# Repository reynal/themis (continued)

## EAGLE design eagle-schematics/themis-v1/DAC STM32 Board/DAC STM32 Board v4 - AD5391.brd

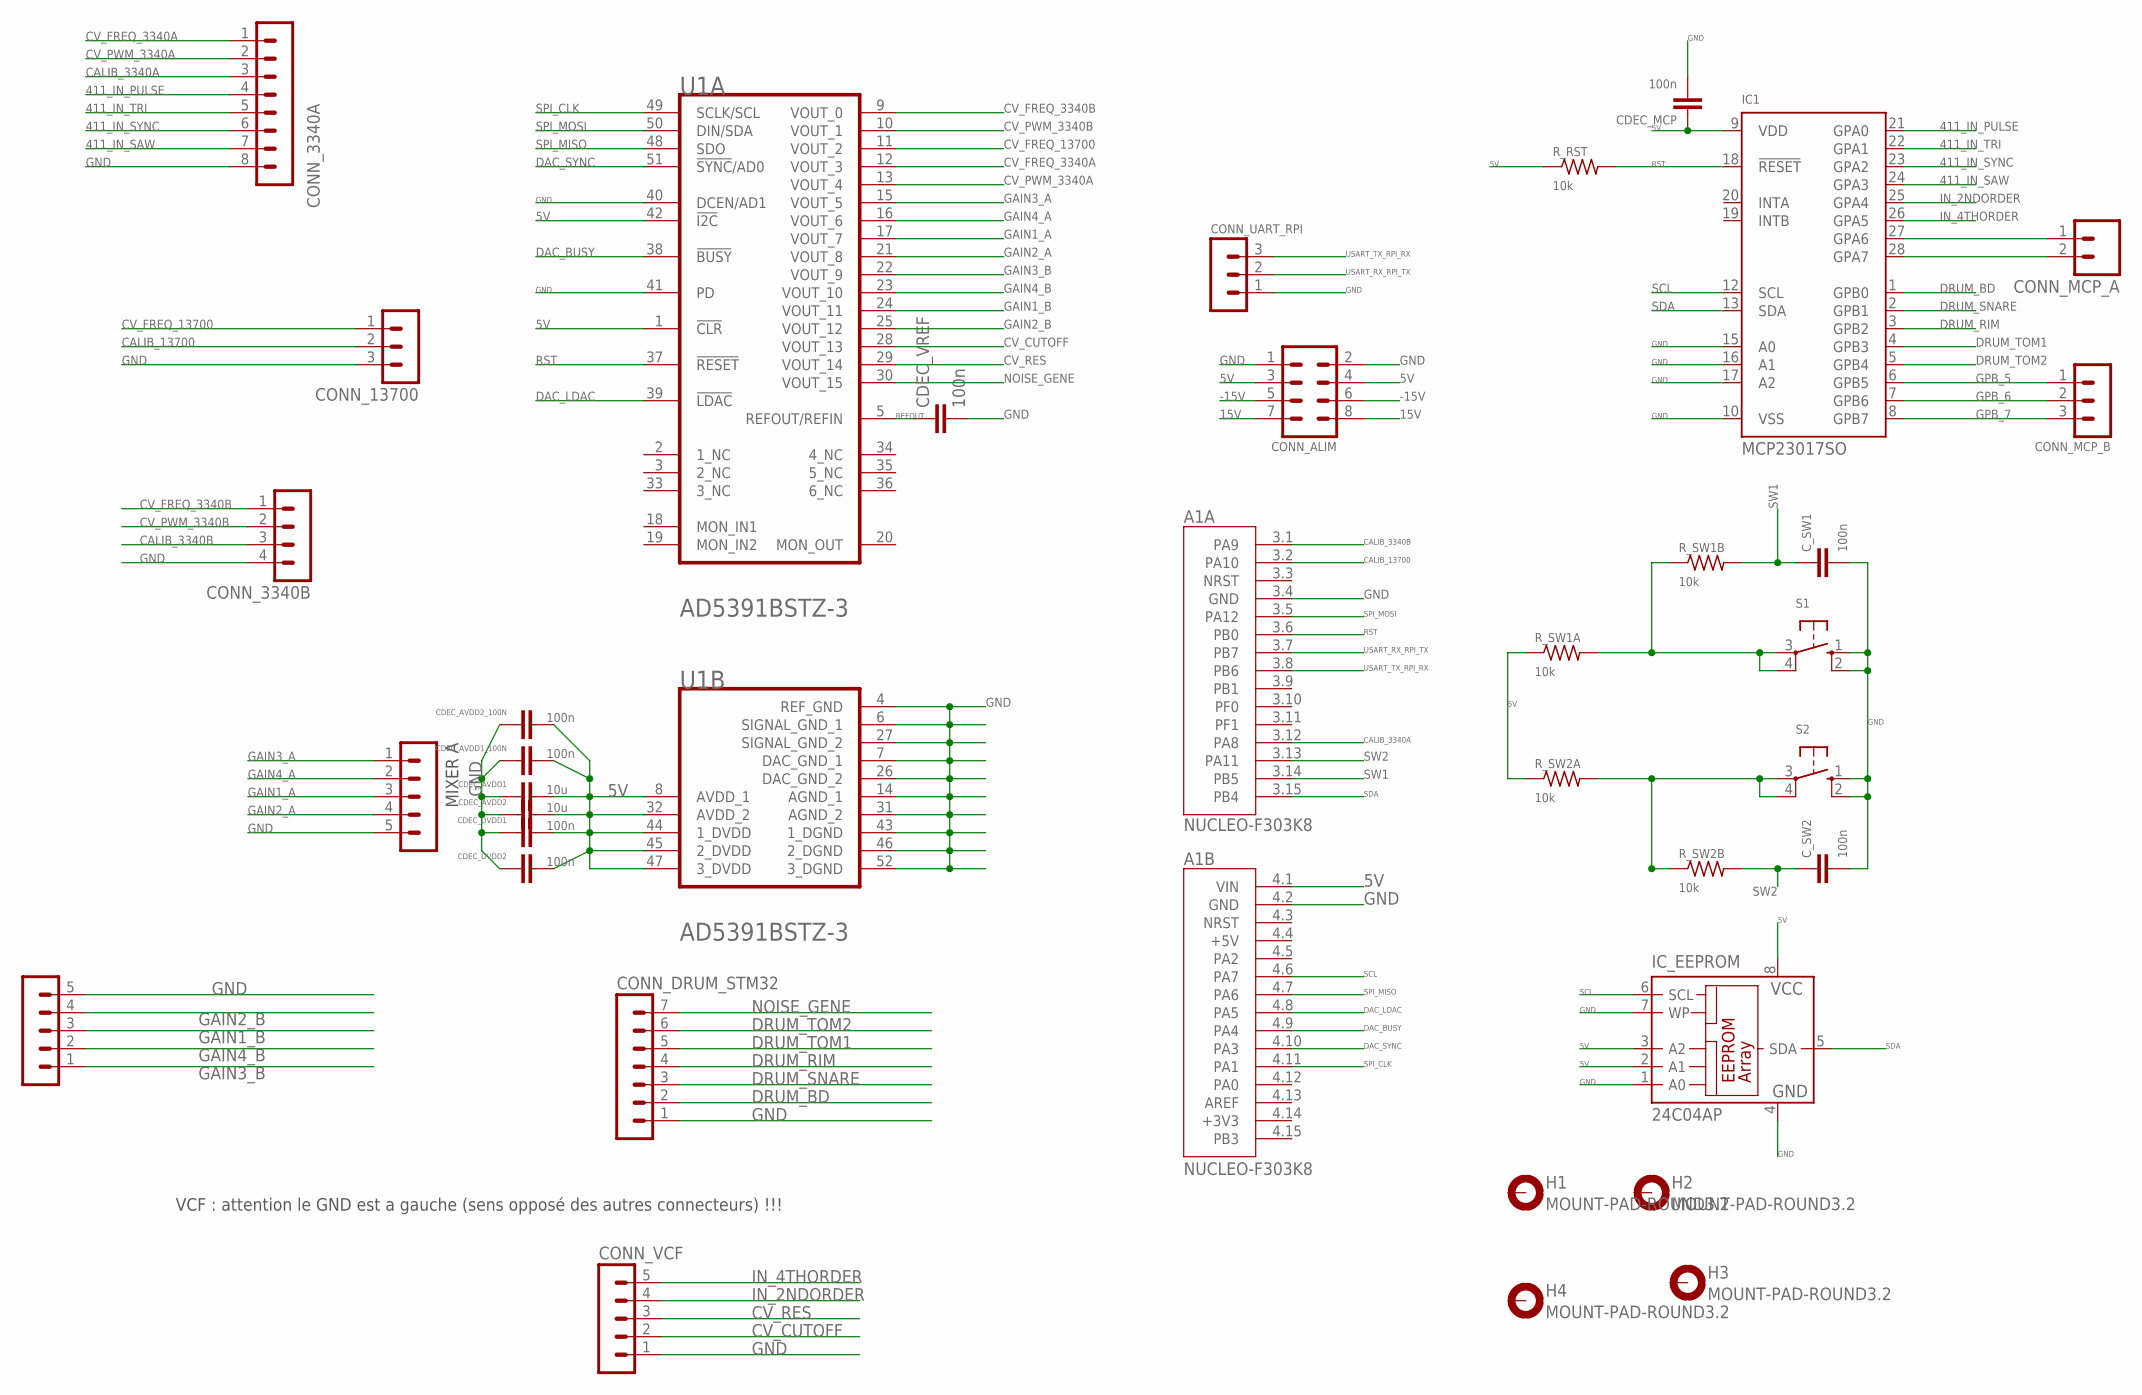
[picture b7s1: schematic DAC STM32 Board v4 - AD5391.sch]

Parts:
A1: NUCLEO-F303K8; MODULE_NUCLEO-F303K8
CDEC_AVDD1, CDEC_AVDD2: 10u; C050-030X075
CDEC_AVDD1_100N, CDEC_AVDD2_100N: 100n; C050-030X075
CDEC_DVDD1: 100n; C075-032X103
CDEC_DVDD2: 100n; C050-030X075
CDEC_MCP: 100n; C075-032X103
CDEC_VREF: 100n; C050-030X075
CONN_3340A: MA08-1
CONN_3340B: MA04-1
CONN_13700: MA03-1
CONN_ALIM: MA04-2
CONN_DRUM_STM32: MA07-1
CONN_MCP_A: M02; 02P
CONN_MCP_B: MA03-1
CONN_MIX_A: MA05-1
CONN_MIX_B: MA05-1
CONN_UART_RPI: MA03-1
CONN_VCF: MA05-1
C_SW1, C_SW2: 100n; C050-030X075
H1, H2, H3, H4: MOUNT-PAD-ROUND3.2; 3,2-PAD
IC1: MCP23017SO; SO28W
IC_EEPROM: 24C04AP; DIL8
R_RST: 10k; 0207/10
R_SW1A, R_SW1B, R_SW2A, R_SW2B: 10k; 0207/10
S1, S2: 10-XX; B3F-10XX
U1: ANALOG_DEVICES_AD5391BSTZ-3ANALOG_DEVICES_AD5391B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; ANALOG_DEVICES_AD5391BSTZ-3_0

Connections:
5V: A1.4.1 (VIN), CDEC_AVDD1.2, CDEC_AVDD1_100N.2, CDEC_AVDD2.2, CDEC_AVDD2_100N.2, CDEC_DVDD1.2, CDEC_DVDD2.2, CDEC_MCP.1, CONN_ALIM.3, CONN_ALIM.4, IC1.9 (VDD), IC_EEPROM.2 (A1), IC_EEPROM.3 (A2), IC_EEPROM.8 (VCC), R_RST.1, R_SW1A.1, R_SW2A.1, U1.1 (!CLR!), U1.8 (AVDD_1), U1.32 (AVDD_2), U1.42 (!I2C!), U1.44 (1_DVDD), U1.45 (2_DVDD), U1.47 (3_DVDD)
15V: CONN_ALIM.7, CONN_ALIM.8
411_IN_PULSE: CONN_3340A.4, IC1.21 (GPA0)
411_IN_SAW: CONN_3340A.7, IC1.24 (GPA3)
411_IN_SYNC: CONN_3340A.6, IC1.23 (GPA2)
411_IN_TRI: CONN_3340A.5, IC1.22 (GPA1)
-15V: CONN_ALIM.5, CONN_ALIM.6
CALIB_3340A: A1.3.12 (PA8), CONN_3340A.3
CALIB_3340B: A1.3.1 (PA9), CONN_3340B.3
CALIB_13700: A1.3.2 (PA10), CONN_13700.2
CV_CUTOFF: CONN_VCF.2, U1.28 (VOUT_13)
CV_FREQ_3340A: CONN_3340A.1, U1.12 (VOUT_3)
CV_FREQ_3340B: CONN_3340B.1, U1.9 (VOUT_0)
CV_FREQ_13700: CONN_13700.1, U1.11 (VOUT_2)
CV_PWM_3340A: CONN_3340A.2, U1.13 (VOUT_4)
CV_PWM_3340B: CONN_3340B.2, U1.10 (VOUT_1)
CV_RES: CONN_VCF.3, U1.29 (VOUT_14)
DAC_BUSY: A1.4.9 (PA4), U1.38 (!BUSY!)
DAC_LDAC: A1.4.8 (PA5), U1.39 (!LDAC!)
DAC_SYNC: A1.4.10 (PA3), U1.51 (!SYNC!/AD0)
DRUM_BD: CONN_DRUM_STM32.2, IC1.1 (GPB0)
DRUM_RIM: CONN_DRUM_STM32.4, IC1.3 (GPB2)
DRUM_SNARE: CONN_DRUM_STM32.3, IC1.2 (GPB1)
DRUM_TOM1: CONN_DRUM_STM32.5, IC1.4 (GPB3)
DRUM_TOM2: CONN_DRUM_STM32.6, IC1.5 (GPB4)
GAIN1_A: CONN_MIX_A.3, U1.17 (VOUT_7)
GAIN1_B: CONN_MIX_B.3, U1.24 (VOUT_11)
GAIN2_A: CONN_MIX_A.4, U1.21 (VOUT_8)
GAIN2_B: CONN_MIX_B.4, U1.25 (VOUT_12)
GAIN3_A: CONN_MIX_A.1, U1.15 (VOUT_5)
GAIN3_B: CONN_MIX_B.1, U1.22 (VOUT_9)
GAIN4_A: CONN_MIX_A.2, U1.16 (VOUT_6)
GAIN4_B: CONN_MIX_B.2, U1.23 (VOUT_10)
GND: A1.3.4 (GND), A1.4.2 (GND), CDEC_AVDD1.1, CDEC_AVDD1_100N.1, CDEC_AVDD2.1, CDEC_AVDD2_100N.1, CDEC_DVDD1.1, CDEC_DVDD2.1, CDEC_MCP.2, CDEC_VREF.2, CONN_3340A.8, CONN_3340B.4, CONN_13700.3, CONN_ALIM.1, CONN_ALIM.2, CONN_DRUM_STM32.1, CONN_MIX_A.5, CONN_MIX_B.5, CONN_UART_RPI.1, CONN_VCF.1, C_SW1.2, C_SW2.2, IC1.10 (VSS), IC1.15 (A0), IC1.16 (A1), IC1.17 (A2), IC_EEPROM.1 (A0), IC_EEPROM.4 (GND), IC_EEPROM.7 (WP), S1.1 (S), S1.2 (S1), S2.1 (S), S2.2 (S1), U1.4 (REF_GND), U1.6 (SIGNAL_GND_1), U1.7 (DAC_GND_1), U1.14 (AGND_1), U1.26 (DAC_GND_2), U1.27 (SIGNAL_GND_2), U1.31 (AGND_2), U1.40 (DCEN/AD1), U1.41 (PD), U1.43 (1_DGND), U1.46 (2_DGND), U1.52 (3_DGND)
GPB_5: CONN_MCP_B.1, IC1.6 (GPB5)
GPB_6: CONN_MCP_B.2, IC1.7 (GPB6)
GPB_7: CONN_MCP_B.3, IC1.8 (GPB7)
IN_2NDORDER: CONN_VCF.4, IC1.25 (GPA4)
IN_4THORDER: CONN_VCF.5, IC1.26 (GPA5)
unnamed: CONN_MCP_A.1, IC1.27 (GPA6)
unnamed: R_SW1A.2, R_SW1B.1, S1.3, S1.4 (P1)
unnamed: CONN_MCP_A.2, IC1.28 (GPA7)
unnamed: R_SW2A.2, R_SW2B.1, S2.3, S2.4 (P1)
NOISE_GENE: CONN_DRUM_STM32.7, U1.30 (VOUT_15)
REFOUT: CDEC_VREF.1, U1.5 (REFOUT/REFIN)
RST: A1.3.6 (PB0), IC1.18 (!RESET), R_RST.2, U1.37 (!RESET!)
SCL: A1.4.6 (PA7), IC1.12 (SCL), IC_EEPROM.6 (SCL)
SDA: A1.3.15 (PB4), IC1.13 (SDA), IC_EEPROM.5 (SDA)
SPI_CLK: A1.4.11 (PA1), U1.49 (SCLK/SCL)
SPI_MISO: A1.4.7 (PA6), U1.48 (SDO)
SPI_MOSI: A1.3.5 (PA12), U1.50 (DIN/SDA)
SW1: A1.3.14 (PB5), C_SW1.1, R_SW1B.2
SW2: A1.3.13 (PA11), C_SW2.1, R_SW2B.2
USART_RX_RPI_TX: A1.3.7 (PB7), CONN_UART_RPI.2
USART_TX_RPI_RX: A1.3.8 (PB6), CONN_UART_RPI.3

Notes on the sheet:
MIXER A
VCF : attention le GND est a gauche (sens opposé des autres connecteurs) !!!

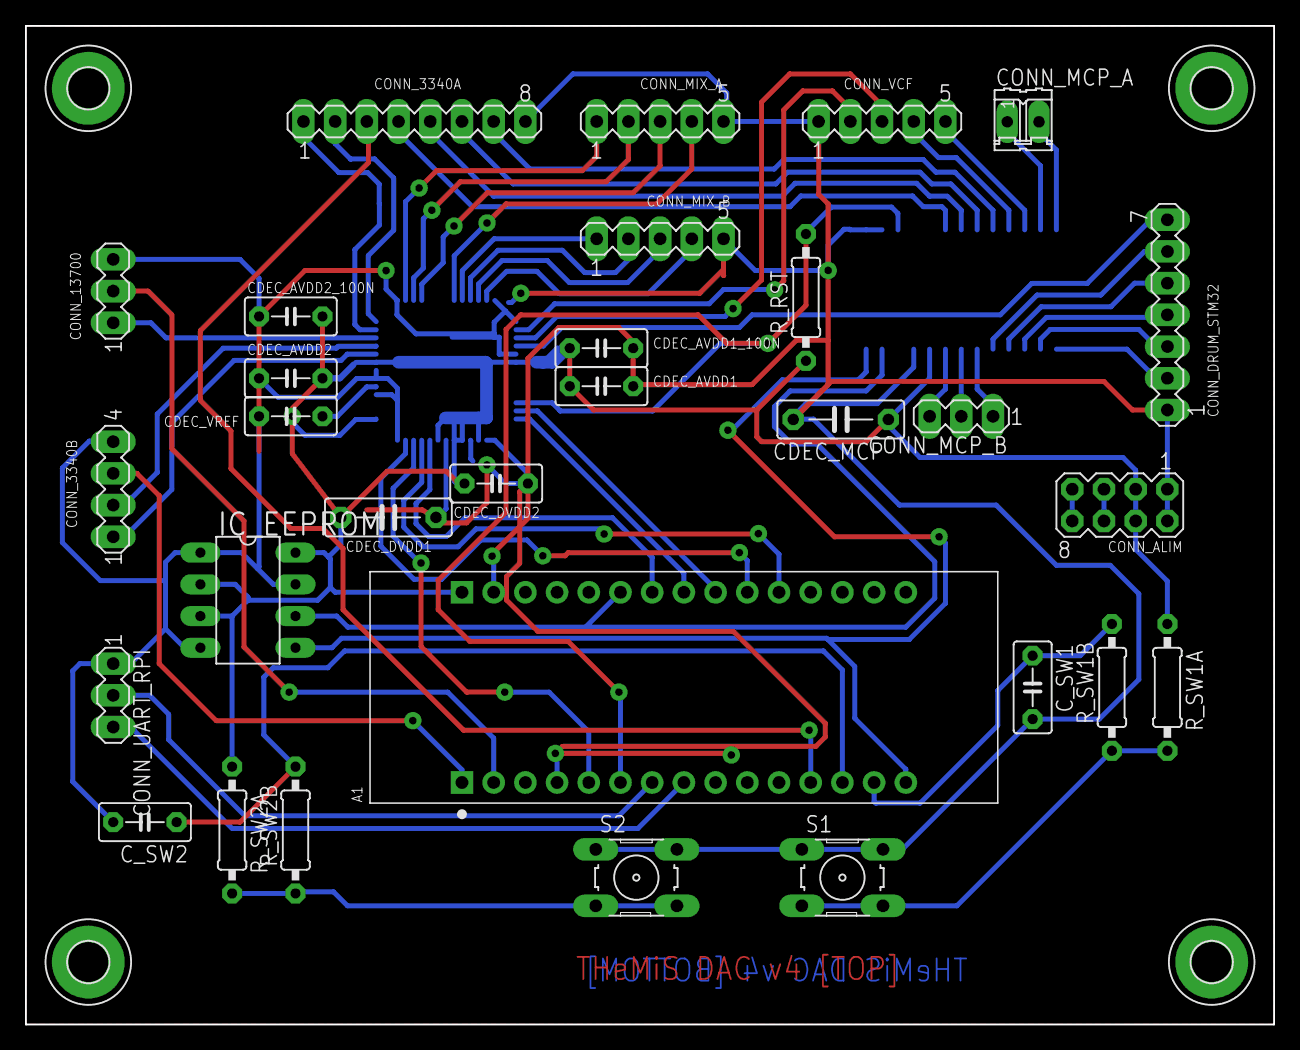
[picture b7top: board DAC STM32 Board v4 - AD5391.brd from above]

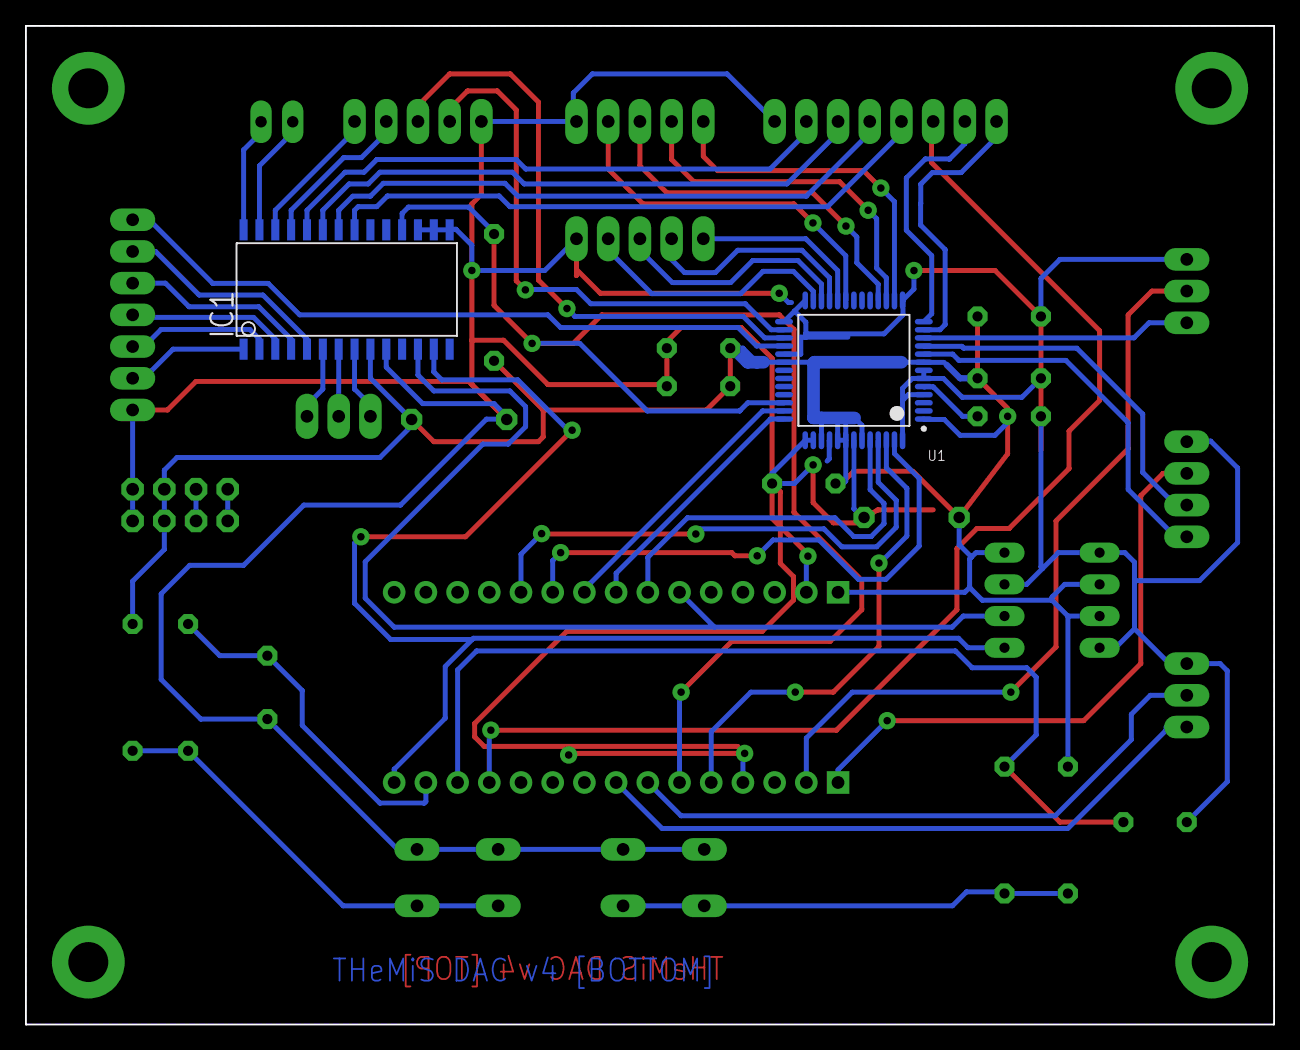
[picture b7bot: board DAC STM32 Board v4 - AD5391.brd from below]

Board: 2 copper layers, 100.0 x 80.0 mm, 36 parts (2 on the bottom side), 55 nets.
